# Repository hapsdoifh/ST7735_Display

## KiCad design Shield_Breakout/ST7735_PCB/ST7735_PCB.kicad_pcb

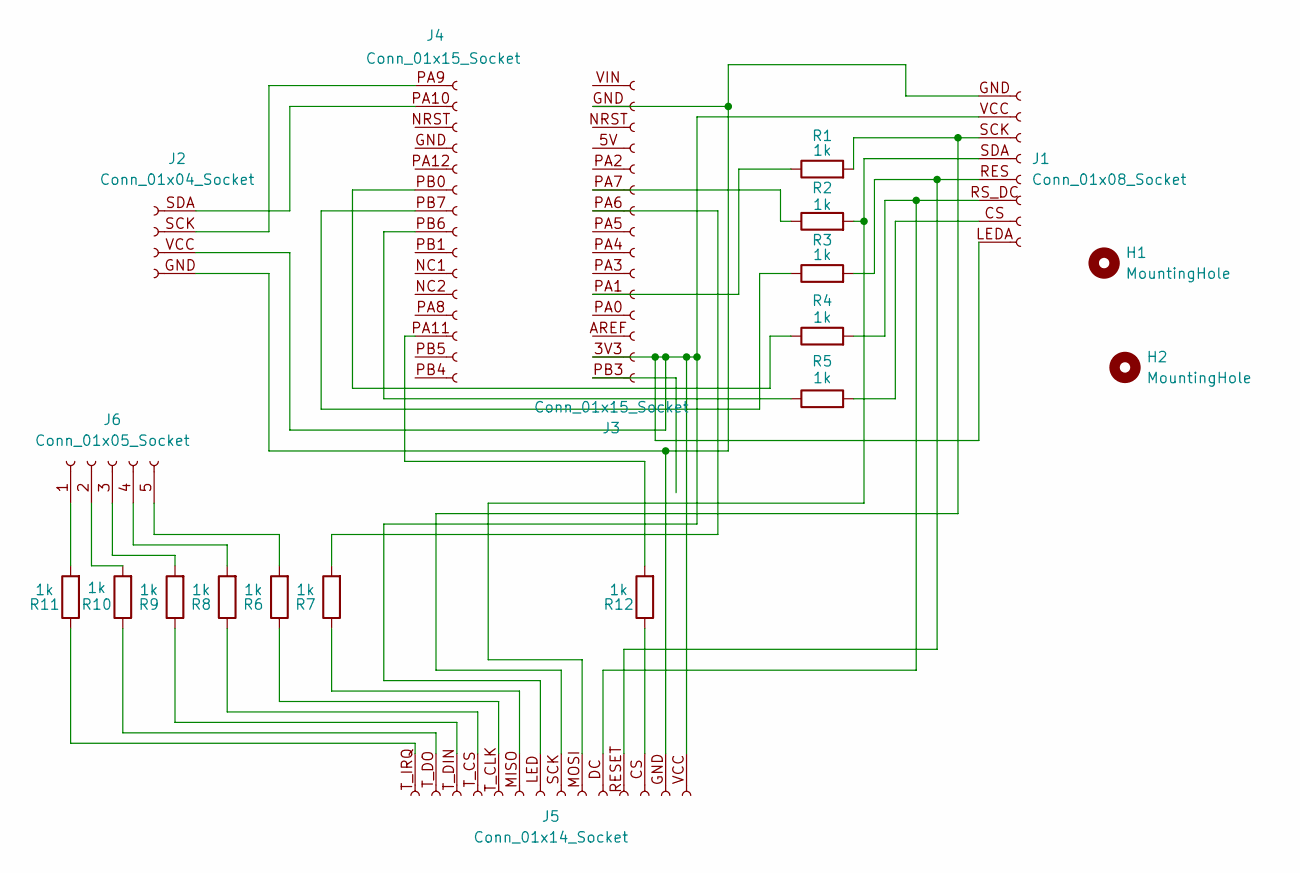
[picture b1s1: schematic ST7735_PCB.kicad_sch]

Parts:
H1, H2: MountingHole; MountingHole_3.2mm_M3_DIN965_Pad_TopBottom
J1: Conn_01x08_Socket; ST7735_MOUNT
J2: Conn_01x04_Socket; I2C_PINS
J3: Conn_01x15_Socket; STM32PIN_RIGHT
J4: Conn_01x15_Socket; STM32PIN_LEFT
J5: Conn_01x14_Socket; ILI9341_MOUNT
J6: Conn_01x05_Socket; PinSocket_1x05_P2.54mm_Vertical
R1, R2, R3, R4, R5, R6, R7, R8, R9, R10, R11, R12: 1k; R_Axial_DIN0207_L6.3mm_D2.5mm_P7.62mm_Horizontal

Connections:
unnamed: J1.GND (Pin_1), J2.GND (Pin_1), J3.GND (Pin_2), J5.GND (Pin_2)
unnamed: J1.LEDA (Pin_8), J1.VCC (Pin_2), J2.VCC (Pin_2), J3.3V3 (Pin_14), J5.LED (Pin_8), J5.VCC (Pin_1)
unnamed: J1.SCK (Pin_3), J5.SCK (Pin_7), R1.2
unnamed: J1.SDA (Pin_4), J5.MOSI (Pin_6), R2.2
unnamed: J1.RES (Pin_5), J5.RESET (Pin_4), R3.2
unnamed: J1.RS_DC (Pin_6), J5.DC (Pin_5), R4.2
unnamed: J1.CS (Pin_7), R5.2
unnamed: J2.SCK (Pin_3), J4.PA9 (Pin_1)
unnamed: J2.SDA (Pin_4), J4.PA10 (Pin_2)
unnamed: J3.PA7 (Pin_6), R2.1
unnamed: J3.PA6 (Pin_7), R7.2
unnamed: J3.PA1 (Pin_11), R1.1
unnamed: J4.PB0 (Pin_6), R4.1
unnamed: J4.PB7 (Pin_7), R3.1
unnamed: J4.PB6 (Pin_8), R5.1
unnamed: J4.PA11 (Pin_13), R12.2
unnamed: J5.CS (Pin_3), R12.1
unnamed: J5.MISO (Pin_9), R7.1
unnamed: J5.T_CLK (Pin_10), R6.1
unnamed: J5.T_CS (Pin_11), R8.1
unnamed: J5.T_DIN (Pin_12), R9.1
unnamed: J5.T_DO (Pin_13), R10.1
unnamed: J5.T_IRQ (Pin_14), R11.1
unnamed: J6.1, R11.2
unnamed: J6.2, R10.2
unnamed: J6.3, R9.2
unnamed: J6.4, R8.2
unnamed: J6.5, R6.2

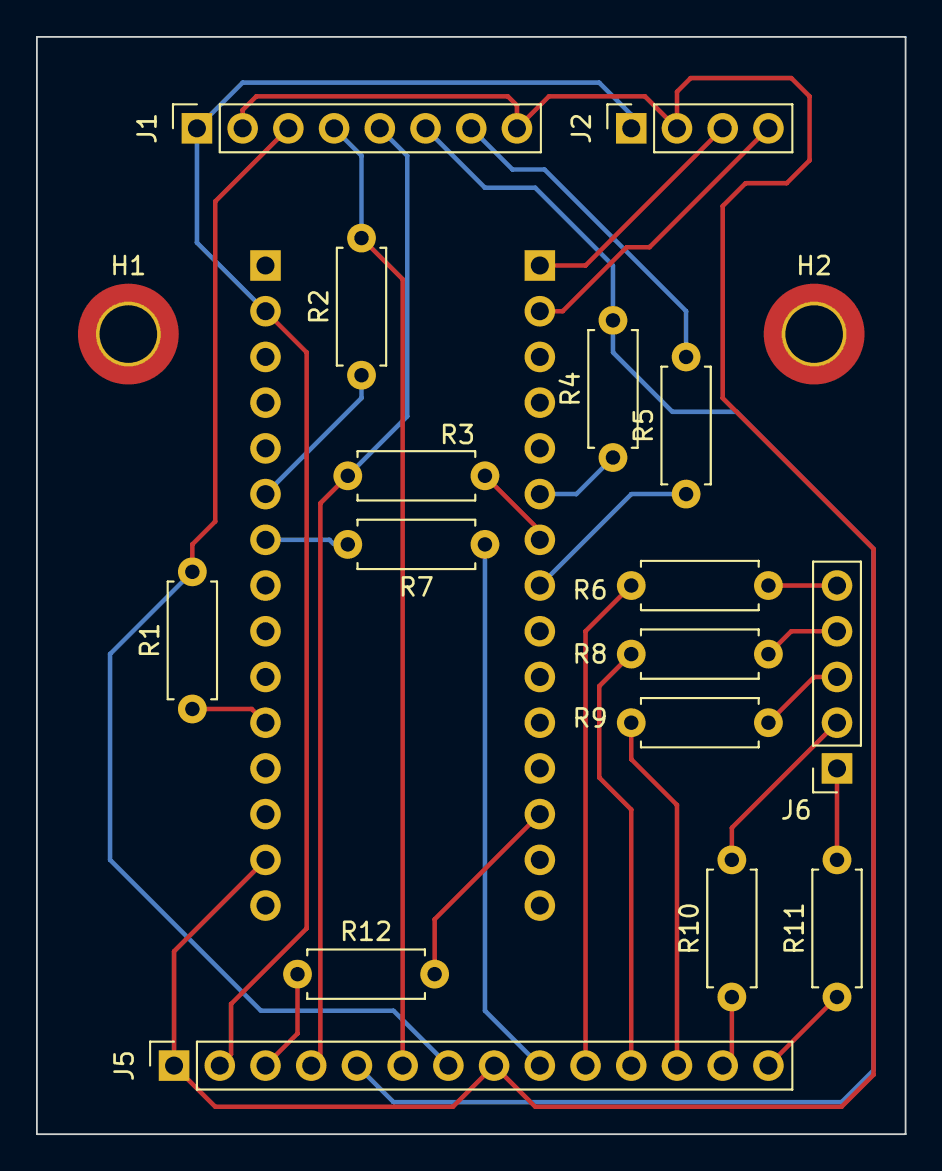
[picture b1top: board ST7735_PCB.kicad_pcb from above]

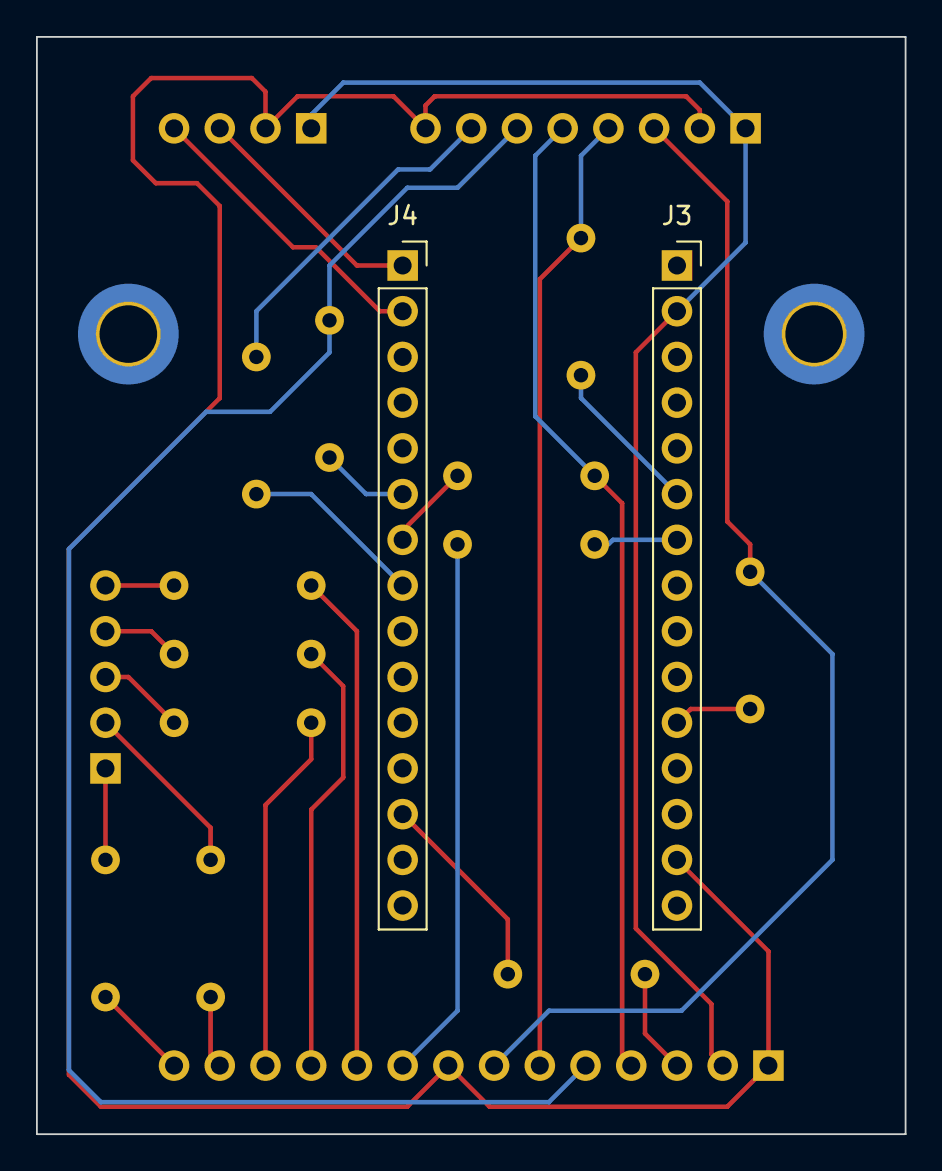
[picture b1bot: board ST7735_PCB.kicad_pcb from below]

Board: 2 copper layers, 48.3 x 61.0 mm, 20 parts (2 on the bottom side), 28 nets.

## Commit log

2024-03-31 Initial commits Initializes display sets color mode 16 bit sets addressing mode write one 4 pixel white line
2024-03-31 Added color control Added draw pixel Cleaned up functions
2024-03-31 Added drawline and draw rect functionality
2024-04-01 Fixed lines and rectangle funtions >
2024-04-01 Added properly working draw ellipse function
2024-04-04 Added thickness option for Arduino Driver Added STM32 code
2024-04-06 Ported over to STM32L432KC
2024-04-06 Added Fonts
2024-04-08 Added ability to draw images to the screen
2024-04-14 Added KICAD PCB files
2024-04-16 Added text box and color features
    TODO:
    The current RGB color is actuall BRG for some reason, correct this foolishness
2024-04-16 Fixed the color issue with the text issue was I was passing in uint16_t and calling transfer 2 bytes instead of using an uint8_t[2] array TODO: investigate why passing in the uint16_t doesn't work Is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
    0000111111110000? LSB of less significant byte first through MSB of less significant byte
    then LSB thru MSB of most significant byte?
2024-04-17 Start implementing class to clean up driver design
2024-04-27 Added OOP Driver Class design to clean up the code
2025-01-17 Added support for esp32c3
2025-01-18 Removed unused functions
2025-01-19 Added RTOS functionlities
